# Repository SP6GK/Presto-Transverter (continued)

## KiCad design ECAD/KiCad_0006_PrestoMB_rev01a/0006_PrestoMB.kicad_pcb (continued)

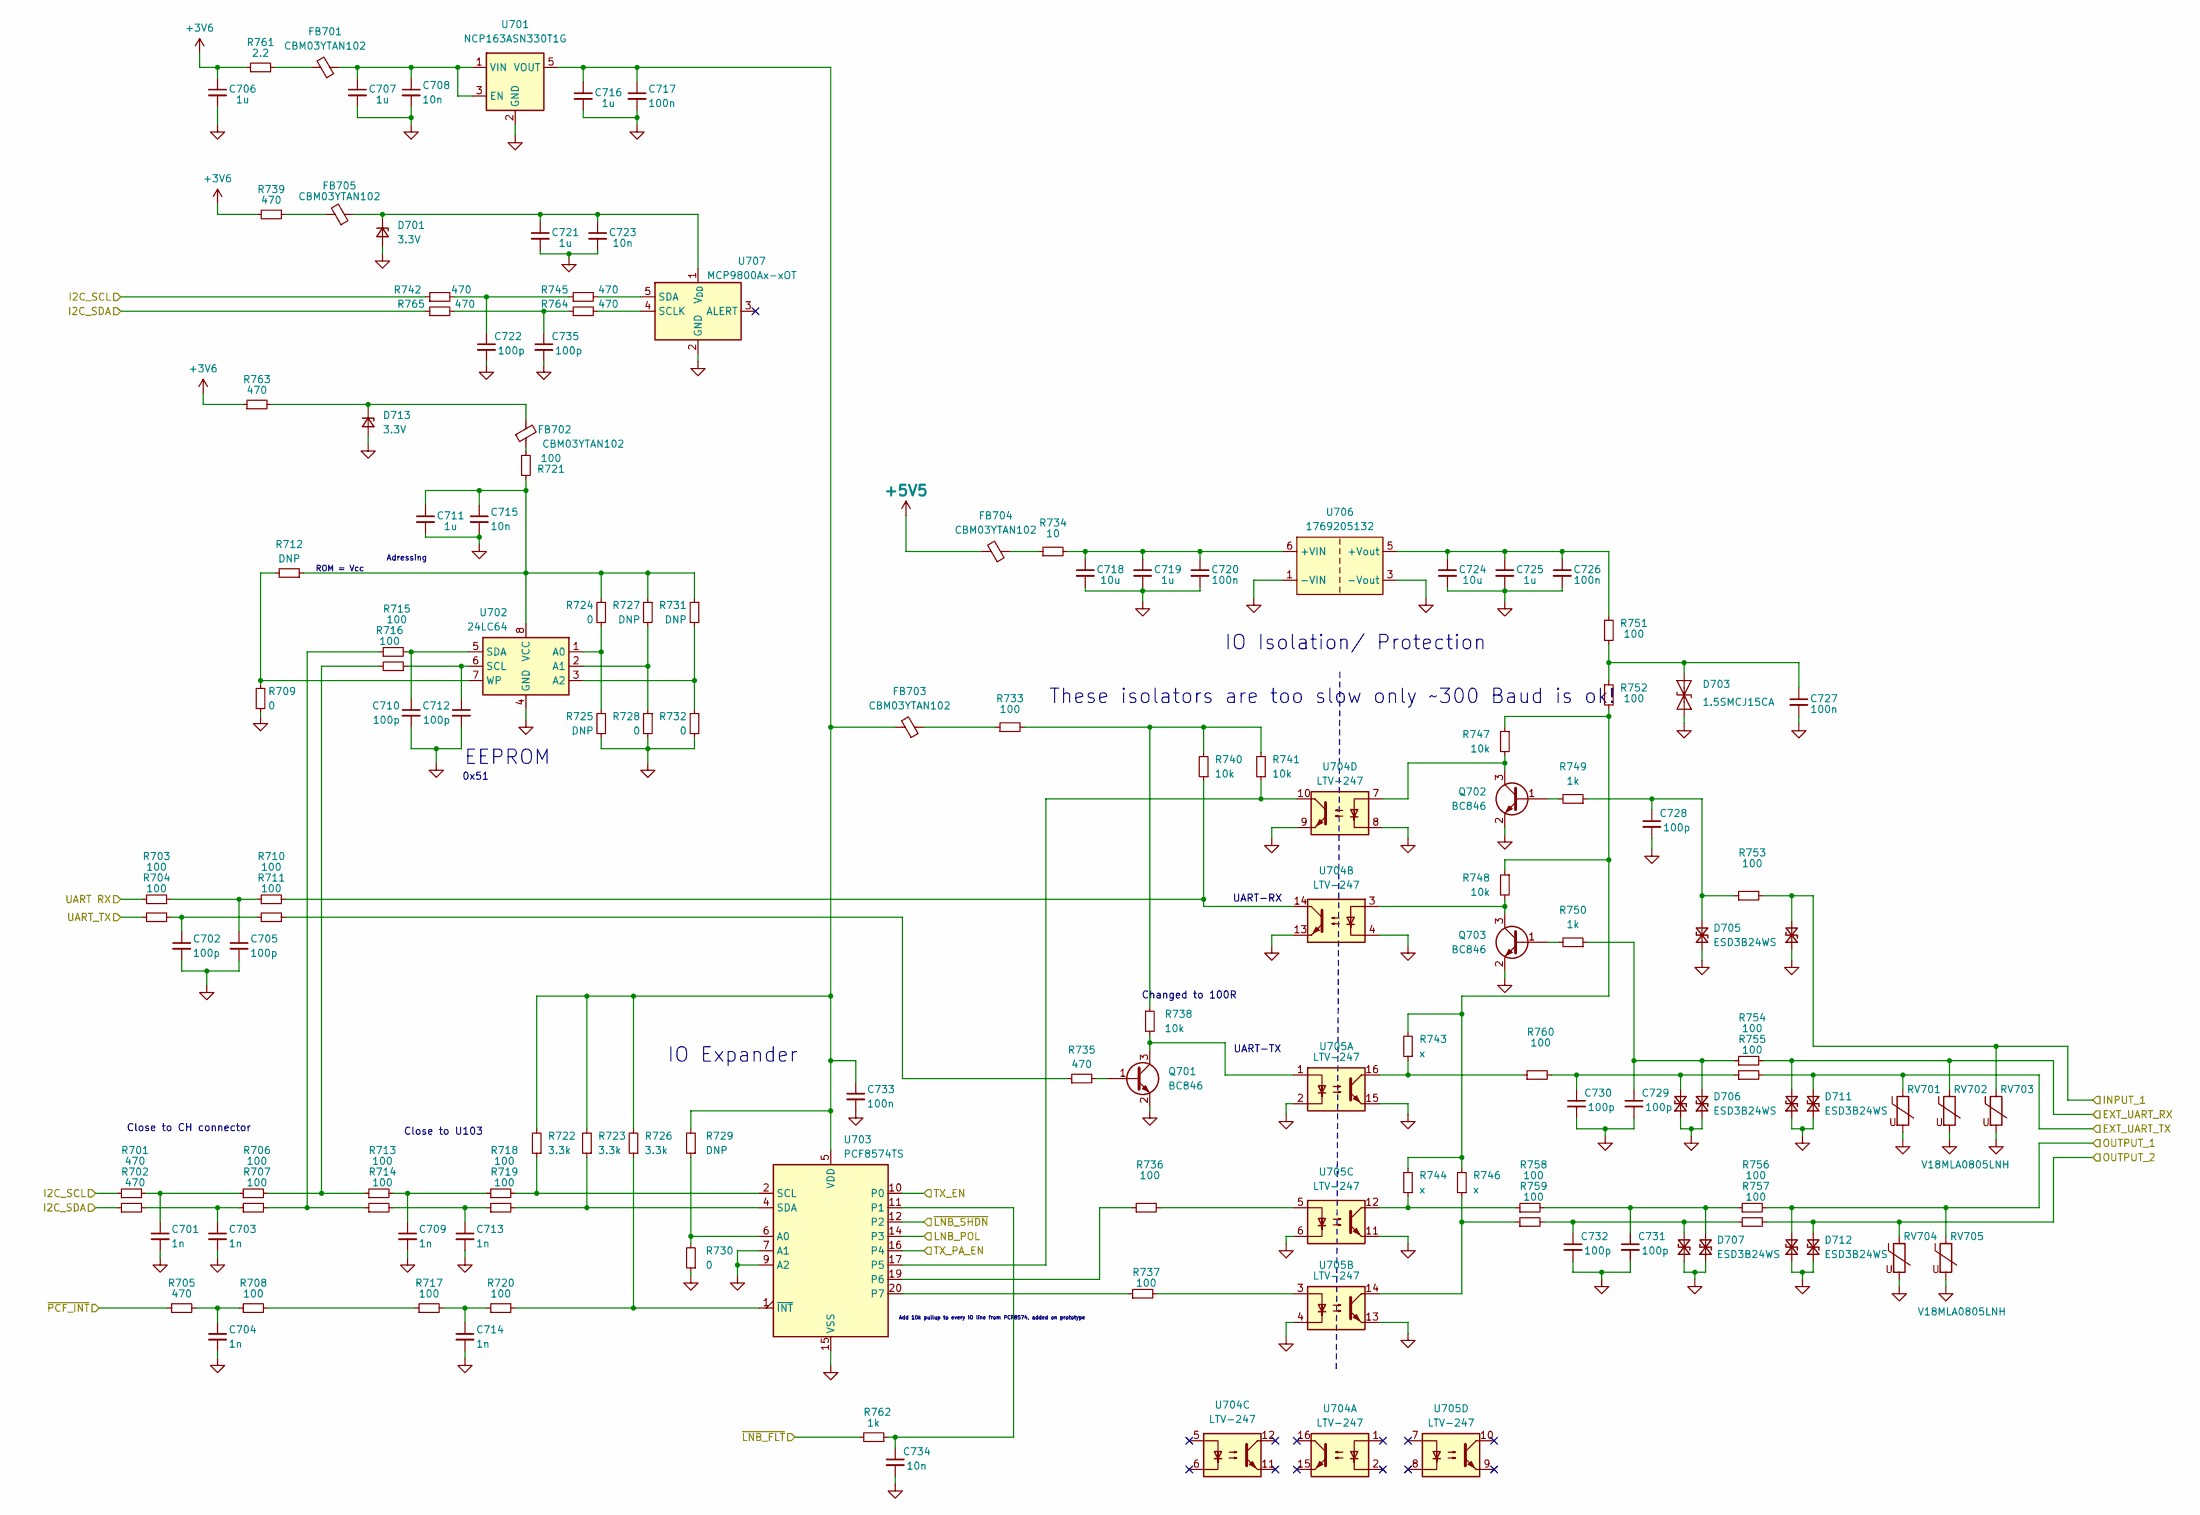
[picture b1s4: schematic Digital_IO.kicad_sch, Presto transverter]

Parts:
C701, C703, C704, C709, C713, C714: 1n; C_0402_1005Metric_Pad0.74x0.62mm_HandSolder
C702, C705, C710, C712, C722, C735: 100p; C_0402_1005Metric_Pad0.74x0.62mm_HandSolder
C706, C707, C711, C716, C719, C721, C725: 1u; C_0603_1608Metric_Pad1.08x0.95mm_HandSolder
C708, C715, C723: 10n; C_0603_1608Metric_Pad1.08x0.95mm_HandSolder
C717, C720, C726, C727, C733: 100n; C_0603_1608Metric_Pad1.08x0.95mm_HandSolder
C718, C724: 10u; C_1206_3216Metric_Pad1.33x1.80mm_HandSolder
C728, C729, C730, C731, C732: 100p; R_0603_1608Metric
C734: 10n; C_0402_1005Metric_Pad0.74x0.62mm_HandSolder
D701, D713: 3.3V; D_SOD-123F
D702, D704, D705, D706, D707, D708, D709, D710, D711, D712: ESD3B24WS; D_SOD-323_HandSoldering
D703: 1.5SMCJ15CA; D_SMA
FB701, FB702, FB703, FB704, FB705: CBM03YTAN102; L_0603_1608Metric_Pad1.05x0.95mm_HandSolder
Q701, Q702, Q703: BC846; SOT-23
R701, R702, R705, R742, R745, R764, R765: 470; R_0402_1005Metric_Pad0.72x0.64mm_HandSolder
R703, R704, R706, R707, R708, R710, R711, R713, R714, R715, R716, R717, R718, R719, R720: 100; R_0402_1005Metric_Pad0.72x0.64mm_HandSolder
R709, R730: 0; R_0603_1608Metric_Pad0.98x0.95mm_HandSolder
R712, R729: DNP; R_0603_1608Metric_Pad0.98x0.95mm_HandSolder
R721, R733, R736, R737, R752, R753, R754, R755, R756, R757, R758, R759, R760: 100; R_0603_1608Metric_Pad0.98x0.95mm_HandSolder
R722, R723, R726: 3.3k; R_0603_1608Metric_Pad0.98x0.95mm_HandSolder
R724, R728, R732: 0; R_0805_2012Metric
R725, R727, R731: DNP; R_0805_2012Metric
R734: 10; R_0603_1608Metric_Pad0.98x0.95mm_HandSolder
R735, R739: 470; R_0603_1608Metric_Pad0.98x0.95mm_HandSolder
R738, R747, R748: 10k; R_0603_1608Metric_Pad0.98x0.95mm_HandSolder
R740, R741: 10k; R_0603_1608Metric
R743, R744, R746: x; R_0603_1608Metric
R749, R750: 1k; R_0603_1608Metric_Pad0.98x0.95mm_HandSolder
R751: 100; R_0805_2012Metric_Pad1.20x1.40mm_HandSolder
R761: 2.2; R_0603_1608Metric_Pad0.98x0.95mm_HandSolder
R762: 1k; R_0402_1005Metric_Pad0.72x0.64mm_HandSolder
R763: 470; R_0805_2012Metric_Pad1.20x1.40mm_HandSolder
RV701, RV702, RV703, RV704, RV705: V18MLA0805LNH; R_0805_2012Metric_Pad1.20x1.40mm_HandSolder
U701: NCP163ASN330T1G; SOT-23-5
U702: 24LC64; SOIC-8_3.9x4.9mm_P1.27mm
U703: PCF8574TS; SSOP-20_4.4x6.5mm_P0.65mm
U704, U705: LTV-247; SOP-16_4.4x10.4mm_P1.27mm
U706: 1769205132
U707: MCP9800Ax-xOT; SOT-23-5

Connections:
3V6: C706.1, R739.1, R761.1, R763.1; also elsewhere on the board
5V5: FB704.2; also elsewhere on the board
/Digital/EXT_UART_RX: D709.2 (A2), R754.2, RV702.1; also elsewhere on the board
/Digital/EXT_UART_TX: D711.2 (A2), R755.2, RV701.1; also elsewhere on the board
/Digital/INPUT_1: D708.2 (A2), R753.2, RV703.1; also elsewhere on the board
/Digital/OUTPUT_1: D710.2 (A2), R756.2, RV705.1; also elsewhere on the board
/Digital/OUTPUT_2: D712.2 (A2), R757.2, RV704.1; also elsewhere on the board
/I2C_SCL: R701.1, R742.1; also elsewhere on the board
/I2C_SDA: R702.1, R765.1; also elsewhere on the board
/LNB_POL: U703.12 (P2); also elsewhere on the board
/TX_EN: U703.10 (P0); also elsewhere on the board
/TX_PA_EN: U703.16 (P4); also elsewhere on the board
/UART RX: R703.2; also elsewhere on the board
/UART_TX: R704.2; also elsewhere on the board
/~LNB_FLT: R762.2; also elsewhere on the board
/~LNB_SHDN: U703.14 (P3); also elsewhere on the board
/~PCF_INT: R705.1; also elsewhere on the board
GND: C701.2, C702.2, C703.2, C704.2, C705.2, C706.2, C707.2, C708.2, C709.2, C710.2, C711.2, C712.2, C713.2, C714.2, C715.2, C716.2, C717.2, C718.2, C719.2, C720.2, C721.2, C722.2, C723.2, C724.2, C725.2, C726.2, C727.2, C728.2, C729.2, C730.2, C731.2, C732.2, C733.2, C734.2, C735.2, D701.2 (A), D702.1 (A1), D703.2 (A2), D704.1 (A1), D705.1 (A1), D706.1 (A1), D707.1 (A1), D708.1 (A1), D709.1 (A1), D710.1 (A1), D711.1 (A1), D712.1 (A1), D713.2 (A), Q701.2 (E), Q702.2 (E), Q703.2 (E), R709.2, R725.2, R728.2, R730.1, R732.2, RV701.2, RV702.2, RV703.2, RV704.2, RV705.2, U701.2 (GND), U702.4 (GND), U703.7 (A1), U703.9 (A2), U703.15 (VSS), U704.4, U704.8, U704.9, U704.13, U705.2, U705.4, U705.6, U705.11, U705.13, U705.15, U706.1 (-VIN), U706.2 (-VIN), U706.3 (-Vout), U706.4 (-Vout), U707.2 (GND); also elsewhere on the board
unnamed: C701.1, R701.2, R706.1
unnamed: C702.1, R704.1, R711.2
unnamed: C703.1, R702.2, R707.1
unnamed: C704.1, R705.2, R708.1
unnamed: C705.1, R703.1, R710.1
unnamed: C709.1, R713.2, R718.1
unnamed: C713.1, R714.2, R719.1
unnamed: C714.1, R717.2, R720.1
unnamed: C718.1, C719.1, C720.1, R734.2, U706.6 (+VIN), U706.7 (+VIN)
unnamed: C722.1, R742.2, R745.1
unnamed: C735.1, R764.1, R765.2
unnamed: C721.1, C723.1, D701.1 (K), FB705.1, U707.1 (V_{DD})
unnamed: C730.1, D702.2 (A2), R755.1, R760.2
unnamed: C727.1, D703.1 (A1), R751.2, R752.1
unnamed: C732.1, D704.2 (A2), R757.1, R759.2
unnamed: C728.1, D705.2 (A2), R749.1, R753.1
unnamed: C729.1, D706.2 (A2), R750.1, R754.1
unnamed: C731.1, D707.2 (A2), R756.1, R758.2
unnamed: D713.1 (K), FB702.2, R763.2
unnamed: FB701.2, R761.2
unnamed: FB702.1, R721.1
unnamed: FB703.1, R733.1
unnamed: FB704.1, R734.1
unnamed: FB705.2, R739.2
unnamed: Q701.1 (B), R735.2
unnamed: Q701.3 (C), R738.2, U705.1
unnamed: Q702.1 (B), R749.2
unnamed: Q702.3 (C), R747.2, U704.7
unnamed: Q703.1 (B), R750.2
unnamed: Q703.3 (C), R748.2, U704.3
unnamed: R706.2, R713.1, R716.2
unnamed: R707.2, R714.1, R715.1
unnamed: R708.2, R717.1
unnamed: R710.2, R740.1, U704.14
unnamed: R711.1, R735.1
unnamed: R733.2, R738.1, R740.2, R741.2
unnamed: R736.2, U705.5
unnamed: R737.2, U705.3
unnamed: R743.1, R760.1, U705.16
unnamed: R743.2, R744.2, R746.2, R747.1, R748.1, R752.2
unnamed: R744.1, R758.1, U705.12
unnamed: R746.1, R759.1, U705.14
unnamed: C707.1, C708.1, FB701.1, U701.1 (VIN), U701.3 (EN)
unnamed: C716.1, C717.1, C733.1, FB703.2, R722.2, R723.2, R726.2, R729.2, U701.5 (VOUT), U703.5 (VDD)
unnamed: R724.2, R725.1, U702.1 (A0)
unnamed: R727.2, R728.1, U702.2 (A1)
unnamed: R731.2, R732.1, U702.3 (A2)
unnamed: C712.1, R716.1, U702.6 (SCL)
unnamed: C710.1, R715.2, U702.5 (SDA)
unnamed: C711.1, C715.1, R712.1, R721.2, R724.1, R727.1, R731.1, U702.8 (VCC)
unnamed: R709.1, R712.2, U702.7 (WP)
unnamed: R729.1, R730.2, U703.6 (A0)
unnamed: C734.1, R762.1, U703.11 (P1)
unnamed: R741.1, U703.17 (P5), U704.10
unnamed: R736.1, U703.19 (P6)
unnamed: R737.1, U703.20 (P7)
unnamed: R718.2, R722.1, U703.2 (SCL)
unnamed: R719.2, R723.1, U703.4 (SDA)
unnamed: R720.2, R726.1, U703.1 (~INT)
unnamed: C724.1, C725.1, C726.1, R751.1, U706.5 (+Vout)
unnamed: R764.2, U707.4 (SCLK)
unnamed: R745.2, U707.5 (SDA)

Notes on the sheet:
ROM = Vcc
IO Isolation/ Protection
0x51
Add 10k pullup to every IO line from PCF8574, added on prototype
Changed to 100R
IO Expander
UART-TX
UART-RX
EEPROM
Adressing
Close to CH connector
Close to U103
These isolators are too slow only ~300 Baud is ok!

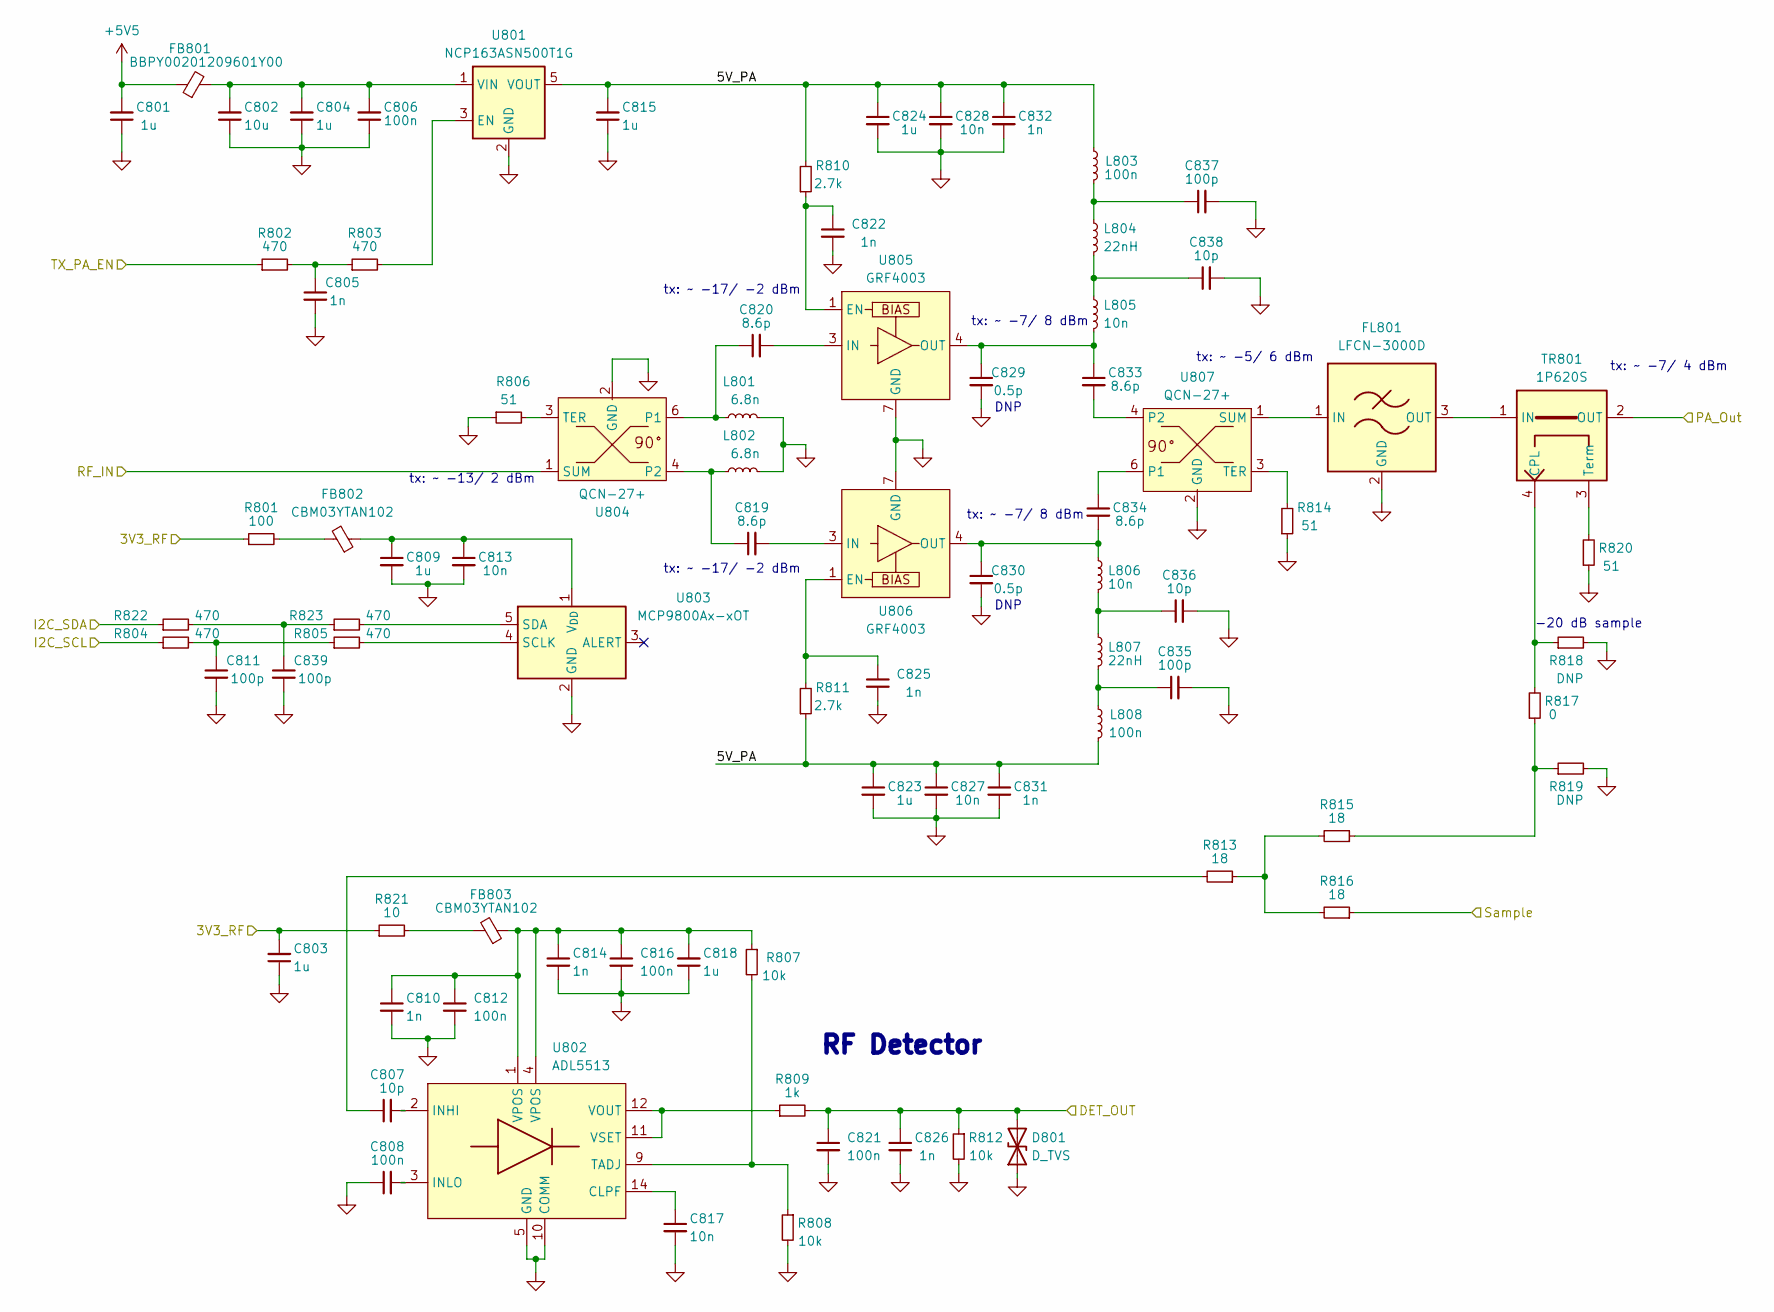
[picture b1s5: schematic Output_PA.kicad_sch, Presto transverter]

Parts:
C801, C803, C804, C809, C815, C818, C823, C824: 1u; C_0603_1608Metric_Pad1.08x0.95mm_HandSolder
C802: 10u; LED_0805_2012Metric
C805: 1n; R_0603_1608Metric
C806, C808, C812, C816, C821: 100n; C_0603_1608Metric_Pad1.08x0.95mm_HandSolder
C807, C836, C838: 10p; C_0603_1608Metric_Pad1.08x0.95mm_HandSolder
C810, C814, C822, C825, C826, C831, C832: 1n; C_0603_1608Metric_Pad1.08x0.95mm_HandSolder
C811, C839: 100p; C_0402_1005Metric_Pad0.74x0.62mm_HandSolder
C813, C817, C827, C828: 10n; C_0603_1608Metric_Pad1.08x0.95mm_HandSolder
C819, C820, C833, C834: 8.6p; C_0603_1608Metric_Pad1.08x0.95mm_HandSolder
C829, C830: 0.5p; C_0603_1608Metric_Pad1.08x0.95mm_HandSolder
C835, C837: 100p; C_0603_1608Metric_Pad1.08x0.95mm_HandSolder
D801: D_TVS; D_SOD-323
FB801: BBPY00201209601Y00; L_0805_2012Metric_Pad1.05x1.20mm_HandSolder
FB802, FB803: CBM03YTAN102; L_0603_1608Metric_Pad1.05x0.95mm_HandSolder
FL801: LFCN-3000D; Filter_Mini-Circuits_FV1206
L801, L802: 6.8n; L_0603_1608Metric_Pad1.05x0.95mm_HandSolder
L803, L808: 100n; L_0603_1608Metric_Pad1.05x0.95mm_HandSolder
L804, L807: 22nH; L_0603_1608Metric_Pad1.05x0.95mm_HandSolder
L805, L806: 10n; L_0603_1608Metric_Pad1.05x0.95mm_HandSolder
R801: 100; R_0603_1608Metric_Pad0.98x0.95mm_HandSolder
R802, R803, R804, R805, R822, R823: 470; R_0402_1005Metric_Pad0.72x0.64mm_HandSolder
R806, R814: 51; R_0805_2012Metric_Pad1.20x1.40mm_HandSolder
R807, R808, R812: 10k; R_0603_1608Metric_Pad0.98x0.95mm_HandSolder
R809: 1k; R_0603_1608Metric_Pad0.98x0.95mm_HandSolder
R810, R811: 2.7k; R_0603_1608Metric_Pad0.98x0.95mm_HandSolder
R813, R815, R816: 18; R_0603_1608Metric_Pad0.98x0.95mm_HandSolder
R817: 0; R_0603_1608Metric_Pad0.98x0.95mm_HandSolder
R818, R819: DNP; R_0603_1608Metric_Pad0.98x0.95mm_HandSolder
R820: 51; R_0603_1608Metric
R821: 10; R_0402_1005Metric_Pad0.72x0.64mm_HandSolder
TR801: 1P620S
U801: NCP163ASN500T1G; SOT-23-5
U802: ADL5513; LFCSP-16-1EP_3x3mm_P0.5mm_EP1.7x1.7mm_ThermalVias
U803: MCP9800Ax-xOT; SOT-23-5
U804, U807: QCN-27+
U805, U806: GRF4003; DFN-6-1EP_2x2mm_P0.5mm_EP0.6x1.37mm

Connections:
3v3_RF: C803.2, R801.1, R821.1; also elsewhere on the board
5V5: C801.2, FB801.1; also elsewhere on the board
/DET_OUT: C821.1, C826.1, D801.2 (A2), R809.2, R812.1; also elsewhere on the board
/I2C_SCL: R804.1; also elsewhere on the board
/I2C_SDA: R822.1; also elsewhere on the board
/Output_PA/5V_PA: C815.2, C823.1, C824.1, C827.1, C828.1, C831.1, C832.1, L803.1, L808.1, R810.2, R811.1, U801.5 (VOUT)
/Output_PA/PA_Out: TR801.2 (OUT); also elsewhere on the board
/Output_PA/RF_IN: U804.1 (SUM); also elsewhere on the board
/Output_PA/Sample: R816.1; also elsewhere on the board
/TX_PA_EN: R802.1; also elsewhere on the board
GND: C801.1, C802.1, C803.1, C804.1, C805.2, C806.1, C808.1, C809.2, C810.2, C811.2, C812.2, C813.2, C814.2, C815.1, C816.2, C817.2, C818.1, C821.2, C822.2, C823.2, C824.2, C825.2, C826.2, C827.2, C828.2, C829.2, C830.2, C831.2, C832.2, C835.2, C836.2, C837.2, C838.2, C839.2, D801.1 (A1), FL801.2 (GND), FL801.4 (GND), L801.2, L802.2, R806.1, R808.2, R812.2, R814.1, R818.2, R819.2, R820.1, U801.2 (GND), U802.5 (GND), U802.6 (GND), U802.7 (GND), U802.8 (GND), U802.10 (COMM), U802.13 (GND), U802.15 (GND), U802.16 (GND), U802.17 (GND), U803.2 (GND), U804.2 (GND), U804.5 (GND), U805.2 (GND), U805.5 (GND), U805.6 (GND), U805.7 (GND), U806.2 (GND), U806.5 (GND), U806.6 (GND), U806.7 (GND), U807.2 (GND), U807.5 (GND); also elsewhere on the board
unnamed: C805.1, R802.2, R803.1
unnamed: C807.1, R813.2
unnamed: C810.1, C812.1, C814.1, C816.1, C818.2, FB803.1, R807.1, U802.1 (VPOS), U802.4 (VPOS)
unnamed: C811.1, R804.2, R805.1
unnamed: C835.1, L807.1, L808.2
unnamed: C836.1, L806.1, L807.2
unnamed: C837.1, L803.2, L804.1
unnamed: C838.1, L804.2, L805.1
unnamed: C839.1, R822.2, R823.1
unnamed: FB802.2, R801.2
unnamed: FB803.2, R821.2
unnamed: FL801.1 (IN), U807.1 (SUM)
unnamed: FL801.3 (OUT), TR801.1 (IN)
unnamed: R813.1, R815.2, R816.2
unnamed: R815.1, R817.1, R819.1
unnamed: R817.2, R818.1, TR801.4 (CPL)
unnamed: R820.2, TR801.3 (Term)
unnamed: R803.2, U801.3 (EN)
unnamed: C802.2, C804.2, C806.2, FB801.2, U801.1 (VIN)
unnamed: C817.1, U802.14 (CLPF)
unnamed: C807.2, U802.2 (INHI)
unnamed: C808.2, U802.3 (INLO)
unnamed: R807.2, R808.1, U802.9 (TADJ)
unnamed: R809.1, U802.11 (VSET), U802.12 (VOUT)
unnamed: R805.2, U803.4 (SCLK)
unnamed: R823.2, U803.5 (SDA)
unnamed: C809.1, C813.1, FB802.1, U803.1 (V_{DD})
unnamed: C820.1, L801.1, U804.6 (P1)
unnamed: C819.1, L802.1, U804.4 (P2)
unnamed: R806.2, U804.3 (TER)
unnamed: C822.1, R810.1, U805.1 (EN)
unnamed: C820.2, U805.3 (IN)
unnamed: C829.1, C833.1, L805.2, U805.4 (OUT)
unnamed: C825.1, R811.2, U806.1 (EN)
unnamed: C819.2, U806.3 (IN)
unnamed: C830.1, C834.2, L806.2, U806.4 (OUT)
unnamed: C834.1, U807.6 (P1)
unnamed: C833.2, U807.4 (P2)
unnamed: R814.2, U807.3 (TER)

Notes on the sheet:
tx: ~ -7/ 8 dBm
-20 dB sample
DNP
tx: ~ -7/ 4 dBm
tx: ~ -5/ 6 dBm
RF Detector
tx: ~ -17/ -2 dBm
tx: ~ -13/ 2 dBm

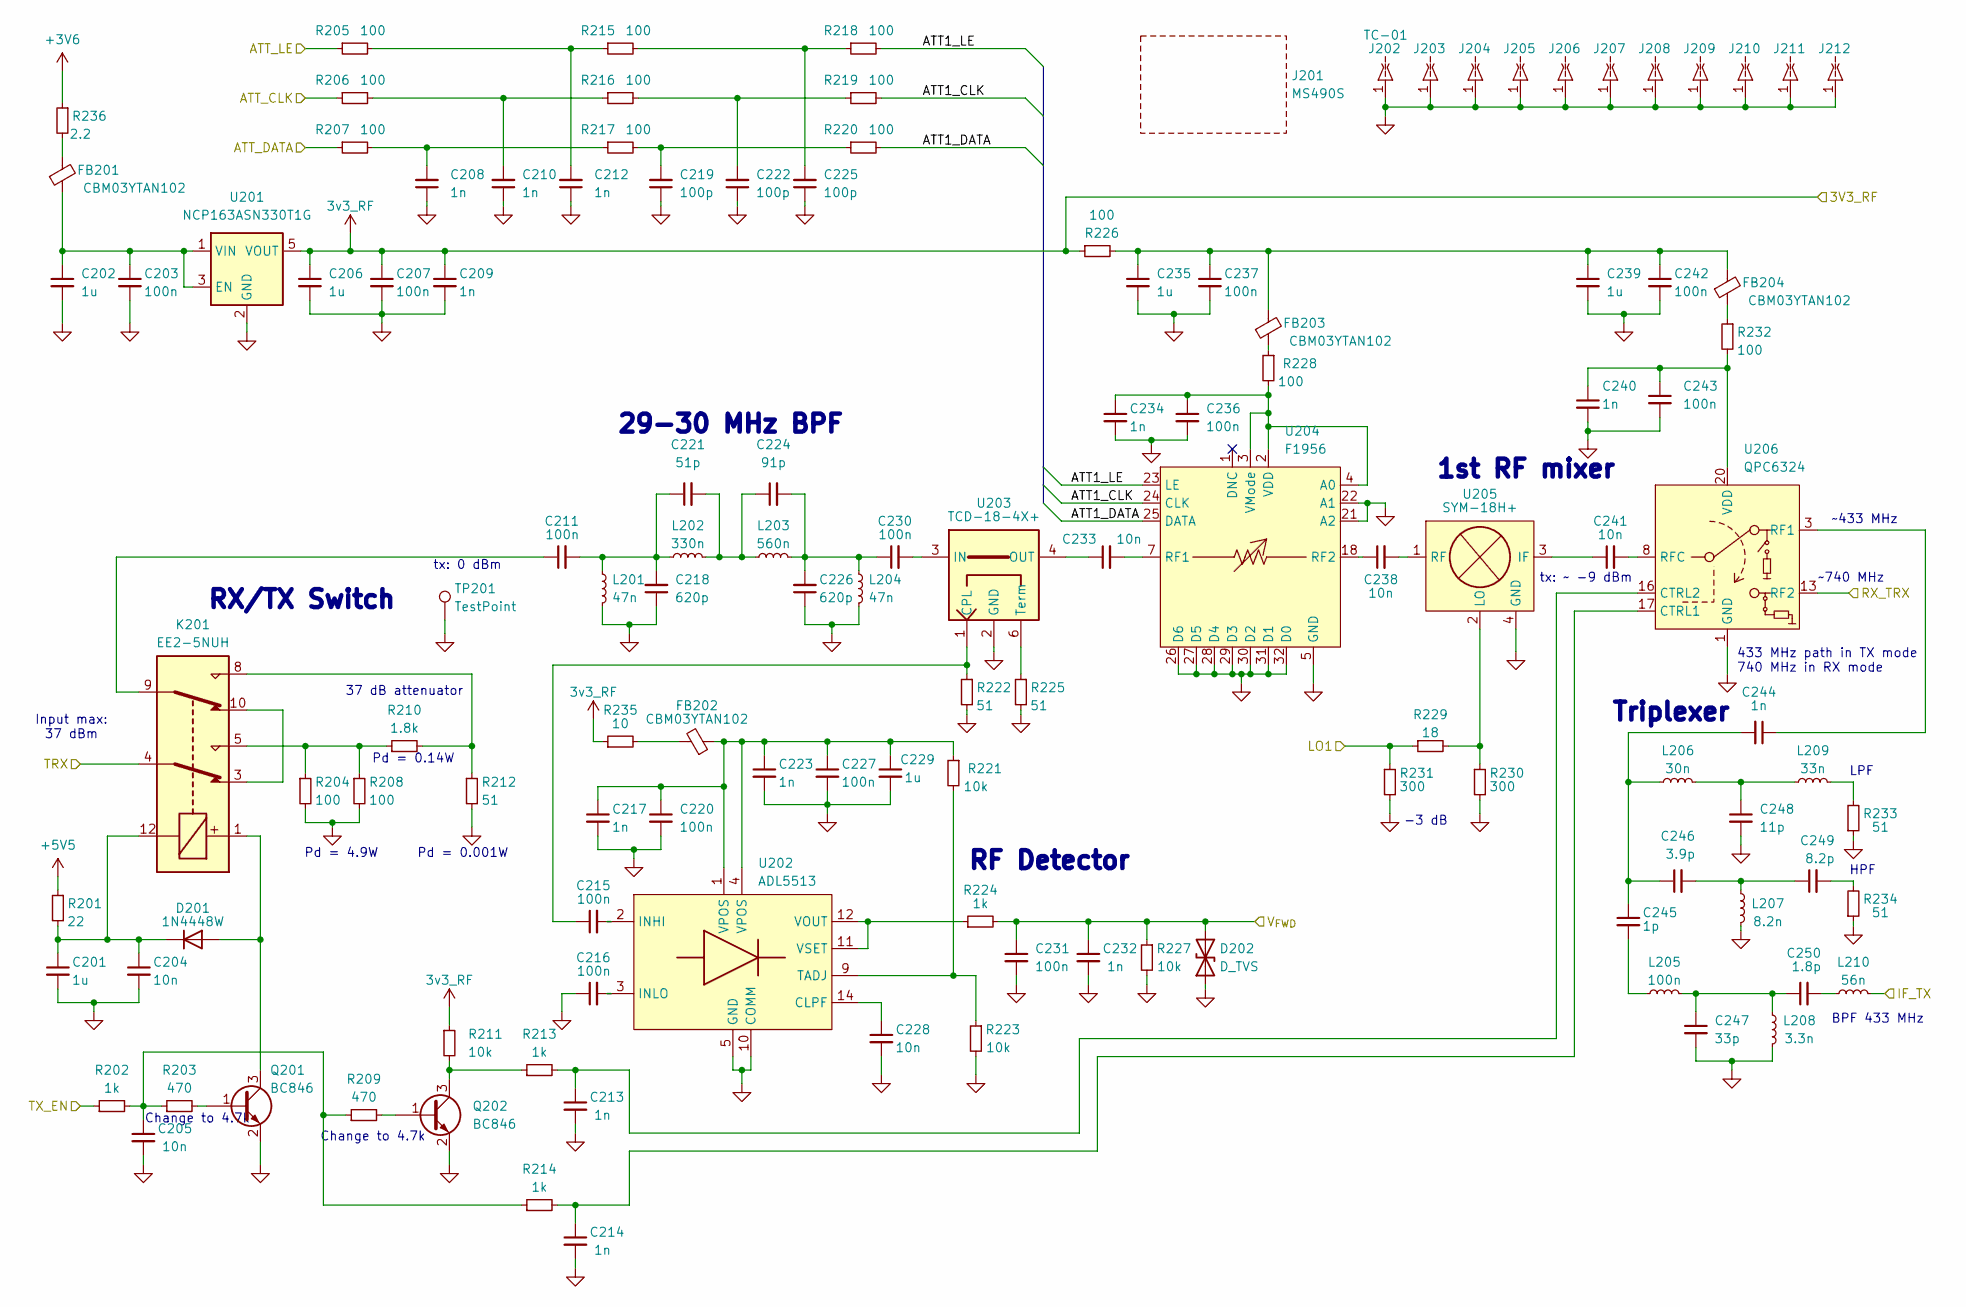
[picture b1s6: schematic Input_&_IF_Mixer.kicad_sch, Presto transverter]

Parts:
C201: 1u; C_0805_2012Metric_Pad1.18x1.45mm_HandSolder
C202, C206, C229, C235, C239: 1u; C_0603_1608Metric_Pad1.08x0.95mm_HandSolder
C203, C207, C211, C215, C216, C220, C227, C230, C231, C237, C242: 100n; C_0603_1608Metric_Pad1.08x0.95mm_HandSolder
C204, C205, C228, C233, C238, C241: 10n; C_0603_1608Metric_Pad1.08x0.95mm_HandSolder
C208, C210, C212, C213, C214, C234, C240: 1n; C_0402_1005Metric_Pad0.74x0.62mm_HandSolder
C209, C217, C223, C232, C244: 1n; C_0603_1608Metric_Pad1.08x0.95mm_HandSolder
C218, C226: 620p; C_0603_1608Metric_Pad1.08x0.95mm_HandSolder
C219, C222, C225: 100p; C_0402_1005Metric_Pad0.74x0.62mm_HandSolder
C221: 51p; C_0603_1608Metric_Pad1.08x0.95mm_HandSolder
C224: 91p; C_0603_1608Metric_Pad1.08x0.95mm_HandSolder
C236, C243: 100n; C_0402_1005Metric_Pad0.74x0.62mm_HandSolder
C245: 1p; C_0603_1608Metric_Pad1.08x0.95mm_HandSolder
C246: 3.9p; C_0603_1608Metric_Pad1.08x0.95mm_HandSolder
C247: 33p; C_0603_1608Metric_Pad1.08x0.95mm_HandSolder
C248: 11p; C_0603_1608Metric_Pad1.08x0.95mm_HandSolder
C249: 8.2p; C_0603_1608Metric_Pad1.08x0.95mm_HandSolder
C250: 1.8p; C_0603_1608Metric_Pad1.08x0.95mm_HandSolder
D201: 1N4448W; D_SOD-123
D202: D_TVS; D_SOD-323
FB201, FB202, FB203, FB204: CBM03YTAN102; L_0603_1608Metric_Pad1.05x0.95mm_HandSolder
J201: MS490S; MS490_Shield
J202, J210, J212: TC-01; TC-01_CLIP_LeaderTech_half
J203, J204, J205, J206, J207, J208, J209, J211: TC-01; TC-01_CLIP_LeaderTech
K201: EE2-5NUH; Relay_DPDT_Kemet_EE2_NUH
L201, L204: 47n; L_1008_2520Metric_Pad1.43x2.20mm_HandSolder
L202: 330n; L_1008_2520Metric_Pad1.43x2.20mm_HandSolder
L203: 560n; L_1008_2520Metric_Pad1.43x2.20mm_HandSolder
L205: 100n; L_0603_1608Metric_Pad1.05x0.95mm_HandSolder
L206: 30n; L_0603_1608Metric_Pad1.05x0.95mm_HandSolder
L207: 8.2n; L_0603_1608Metric_Pad1.05x0.95mm_HandSolder
L208: 3.3n; L_0603_1608Metric_Pad1.05x0.95mm_HandSolder
L209: 33n; L_0603_1608Metric_Pad1.05x0.95mm_HandSolder
L210: 56n; L_0603_1608Metric_Pad1.05x0.95mm_HandSolder
Q201, Q202: BC846; SOT-23
R201: 22; R_1206_3216Metric_Pad1.30x1.75mm_HandSolder
R202, R224: 1k; R_0603_1608Metric_Pad0.98x0.95mm_HandSolder
R203, R209: 470; R_0603_1608Metric_Pad0.98x0.95mm_HandSolder
R204, R208: 100; 3522_custom
R205, R206, R207, R215, R216, R217, R218, R219, R220, R228: 100; R_0402_1005Metric_Pad0.72x0.64mm_HandSolder
R210: 1.8k; R_1210_3225Metric_Pad1.30x2.65mm_HandSolder
R211, R221, R223, R227: 10k; R_0603_1608Metric_Pad0.98x0.95mm_HandSolder
R212: 51; R_1210_3225Metric_Pad1.30x2.65mm_HandSolder
R213, R214: 1k; R_0402_1005Metric_Pad0.72x0.64mm_HandSolder
R222, R225, R233, R234: 51; R_0603_1608Metric_Pad0.98x0.95mm_HandSolder
R226: 100; R_0603_1608Metric_Pad0.98x0.95mm_HandSolder
R229: 18; R_0603_1608Metric_Pad0.98x0.95mm_HandSolder
R230, R231: 300; R_0603_1608Metric_Pad0.98x0.95mm_HandSolder
R232: 100; C_0402_1005Metric_Pad0.74x0.62mm_HandSolder
R235: 10; R_0603_1608Metric_Pad0.98x0.95mm_HandSolder
R236: 2.2; R_0603_1608Metric_Pad0.98x0.95mm_HandSolder
TP201: TestPoint; TestPoint_Pad_4.0x4.0mm
U201: NCP163ASN330T1G; SOT-23-5
U202: ADL5513; LFCSP-16-1EP_3x3mm_P0.5mm_EP1.7x1.7mm_ThermalVias
U203: TCD-18-4X+; TCD-18-4x
U204: F1956; TQFN-32-1EP_5x5mm_P0.5mm_EP3.1x3.1mm
U205: SYM-18H+
U206: QPC6324; QPC6324_QFN20pinSMDQorvo

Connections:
3V6: R236.1; also elsewhere on the board
3v3_RF: C206.1, C207.1, C209.1, R211.1, R226.1, R235.1, U201.5 (VOUT); also elsewhere on the board
5V5: R201.1; also elsewhere on the board
/ATT_CLK: R206.1; also elsewhere on the board
/ATT_DATA: R207.1; also elsewhere on the board
/ATT_LE: R205.1; also elsewhere on the board
/Input_&_IF_Mixer/ATT1_CLK: R219.2, U204.24 (CLK)
/Input_&_IF_Mixer/ATT1_DATA: R220.2, U204.25 (DATA)
/Input_&_IF_Mixer/ATT1_LE: R218.2, U204.23 (LE)
/Input_&_IF_Mixer/IF_TX: L210.2; also elsewhere on the board
/Input_&_IF_Mixer/LO1: R229.1, R231.1; also elsewhere on the board
/Input_&_IF_Mixer/RX_TRX: U206.13 (RF2); also elsewhere on the board
/Input_&_IF_Mixer/TRX: K201.4; also elsewhere on the board
/TX_EN: R202.1; also elsewhere on the board
/V_{FWD}: C231.1, C232.1, D202.2 (A2), R224.2, R227.1; also elsewhere on the board
GND: C201.2, C202.2, C203.2, C204.2, C205.2, C206.2, C207.2, C208.1, C209.2, C210.1, C212.1, C213.2, C214.2, C216.1, C217.2, C218.1, C219.1, C220.2, C222.1, C223.2, C225.1, C226.1, C227.2, C228.2, C229.2, C231.2, C232.2, C234.2, C235.2, C236.2, C237.2, C239.2, C240.2, C242.2, C243.2, C247.2, C248.2, D202.1 (A1), J202.1, J203.1, J204.1, J205.1, J206.1, J207.1, J208.1, J209.1, J210.1, J211.1, J212.1, L201.2, L204.2, L207.2, L208.2, Q201.2 (E), Q202.2 (E), R204.2, R208.2, R212.2, R222.2, R223.2, R225.2, R227.2, R230.2, R231.2, R233.1, R234.1, TP201.1, U201.2 (GND), U202.5 (GND), U202.6 (GND), U202.7 (GND), U202.8 (GND), U202.10 (COMM), U202.13 (GND), U202.15 (GND), U202.16 (GND), U202.17 (GND), U203.2 (GND), U203.5 (GND), U204.5 (GND), U204.6 (GND), U204.8 (GND), U204.9 (GND), U204.10 (GND), U204.11 (GND), U204.12 (GND), U204.13 (GND), U204.14 (GND), U204.15 (GND), U204.16 (GND), U204.17 (GND), U204.19 (GND), U204.20 (GND), U204.21 (A2), U204.22 (A1), U204.26 (D6), U204.27 (D5), U204.28 (D4), U204.29 (D3), U204.30 (D2), U204.31 (D1), U204.32 (D0), U204.33 (GND), U205.4 (GND), U205.5 (GND), U205.6 (GND), U206.1 (GND), U206.2 (GND), U206.4 (GND), U206.5 (GND), U206.6 (GND), U206.7 (GND), U206.9 (GND), U206.10 (GND), U206.11 (GND), U206.12 (GND), U206.14 (GND), U206.15 (GND), U206.18 (GND), U206.19 (GND), U206.21 (GND); also elsewhere on the board
unnamed: C205.1, R202.2, R203.1, R209.1, R214.1
unnamed: C208.2, R207.2, R217.1
unnamed: C210.2, R206.2, R216.1
unnamed: C211.1, K201.9
unnamed: C211.2, C218.2, C221.1, L201.1, L202.1
unnamed: C212.2, R205.2, R215.1
unnamed: C217.1, C220.1, C223.1, C227.1, C229.1, FB202.1, R221.1, U202.1 (VPOS), U202.4 (VPOS)
unnamed: C219.2, R217.2, R220.1
unnamed: C221.2, C224.1, L202.2, L203.1
unnamed: C222.2, R216.2, R219.1
unnamed: C224.2, C226.2, C230.1, L203.2, L204.1
unnamed: C225.2, R215.2, R218.1
unnamed: C235.1, C237.1, C239.1, C242.1, FB203.2, FB204.2, R226.2
unnamed: C245.2, L205.1
unnamed: C246.2, C249.1, L207.1
unnamed: C247.1, C250.1, L205.2, L208.1
unnamed: C248.1, L206.2, L209.1
unnamed: C249.2, R234.2
unnamed: C250.2, L210.1
unnamed: D201.2 (A), K201.1, Q201.3 (C)
unnamed: C201.1, C204.1, D201.1 (K), K201.12, R201.2
unnamed: FB201.2, R236.2
unnamed: FB202.2, R235.2
unnamed: FB203.1, R228.1
unnamed: FB204.1, R232.1
unnamed: K201.5, R204.1, R208.1, R210.1
unnamed: K201.8, R210.2, R212.1
unnamed: K201.3, K201.10
unnamed: L209.2, R233.2
unnamed: Q201.1 (B), R203.2
unnamed: Q202.1 (B), R209.2
unnamed: Q202.3 (C), R211.2, R213.1
unnamed: C202.1, C203.1, FB201.1, U201.1 (VIN), U201.3 (EN)
unnamed: C228.1, U202.14 (CLPF)
unnamed: C215.2, U202.2 (INHI)
unnamed: C216.2, U202.3 (INLO)
unnamed: R221.2, R223.1, U202.9 (TADJ)
unnamed: R224.1, U202.11 (VSET), U202.12 (VOUT)
unnamed: C215.1, R222.1, U203.1 (CPL)
unnamed: C230.2, U203.3 (IN)
unnamed: C233.1, U203.4 (OUT)
unnamed: R225.1, U203.6 (Term)
unnamed: C234.1, C236.1, R228.2, U204.2 (VDD), U204.3 (VMode), U204.4 (A0)
unnamed: C233.2, U204.7 (RF1)
unnamed: C238.1, U204.18 (RF2)
unnamed: C241.1, U205.3 (IF)
unnamed: R229.2, R230.1, U205.2 (LO)
unnamed: C238.2, U205.1 (RF)
unnamed: C214.1, R214.2, U206.17 (CTRL1)
unnamed: C213.1, R213.2, U206.16 (CTRL2)
unnamed: C241.2, U206.8 (RFC)
unnamed: C240.1, C243.1, R232.2, U206.20 (VDD)

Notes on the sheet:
HPF
Pd = 4.9W
Input max: 37 dBm
37 dB attenuator
RF Detector
Pd = 0.001W
RX/TX Switch
tx: ~ -9 dBm
Triplexer
~433 MHz
BPF 433 MHz
LPF
Pd = 0.14W
Change to 4.7k
1st RF mixer
29-30 MHz BPF
433 MHz path in TX mode 740 MHz in RX mode
-3 dB
tx: 0 dBm
~740 MHz
